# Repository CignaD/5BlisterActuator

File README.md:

# 5BlisterActuator
Example Arduino Code and Schematic for a 5 blister plunger

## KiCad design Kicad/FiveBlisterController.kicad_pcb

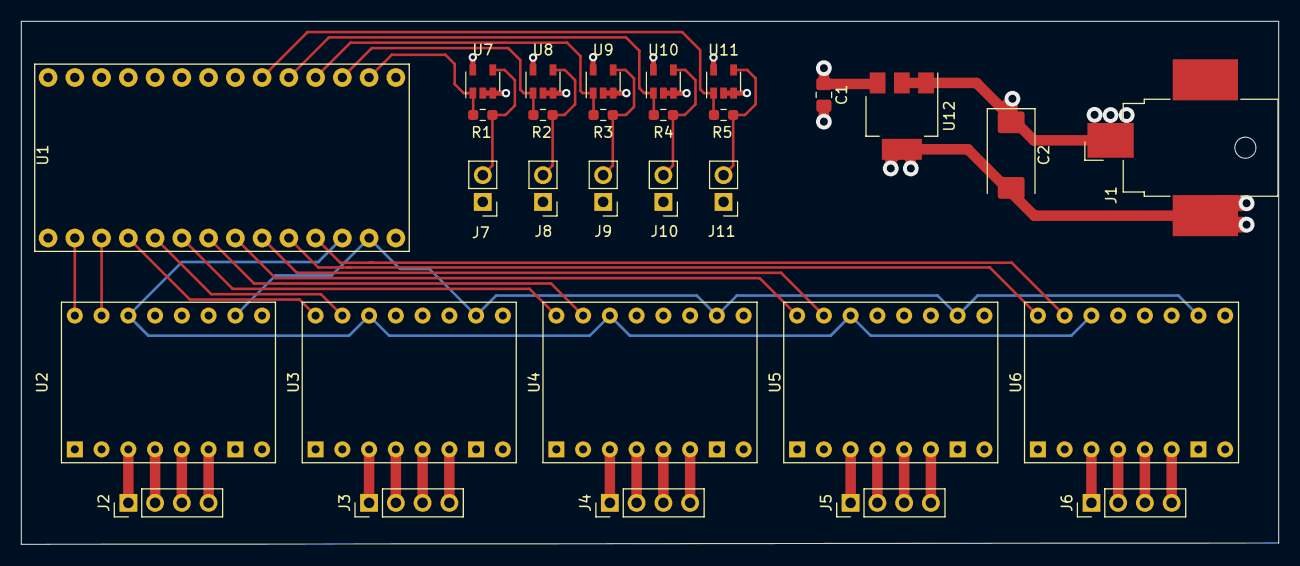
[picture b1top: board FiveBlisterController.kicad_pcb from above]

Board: 4 copper layers, 119.4 x 49.7 mm, 35 parts (0 on the bottom side), 45 nets.

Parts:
C1: 10u; C_0805_2012Metric_Pad1.18x1.45mm_HandSolder
C2: 100u; CP_EIA-7343-30_AVX-N
J1: Barrel_Jack_Switch; BarrelJack_CUI_PJ-036AH-SMT_Horizontal
J2, J3, J4, J5, J6: Conn_01x04_Male; PinHeader_1x04_P2.54mm_Vertical
J7, J8, J9, J10, J11: Conn_01x02_Male; PinHeader_1x02_P2.54mm_Vertical
R1, R2, R3, R4, R5: 2k2; R_0603_1608Metric_Pad0.98x0.95mm_HandSolder
U1: Teensy.32_simple; Teensy3.2_simple
U2, U3, U4, U5, U6: STSPIN220
U2#2, U3#2, U4#2, U5#2, U6#2: Pololu_STSPIN220; Pololu STSPIN220
U7, U8, U9, U10, U11: TLV272; SOT-23-5
U12: MC33375; SOT-223

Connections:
+3V3: C1.1, J7.1, J8.1, J9.1, J10.1, J11.1, U1.26, U2.2, U3.2, U4.2, U5.2, U6.2, U12.3
/Dir0: U1.2, U2.16
/Dir1: U1.4, U3.16
/Dir2: U1.6, U4.16
/Dir3: U1.8, U5.16
/Dir4: U1.10, U6.16
/FSR0: R1.1, U1.16, U7.1
/FSR1: R2.1, U1.17, U8.1
/FSR2: R3.1, U1.18, U9.1
/FSR3: R4.1, U1.19, U10.1
/FSR4: R5.1, U1.20, U11.1
/M1: U1.13, U2.10, U3.10, U4.10, U5.10, U6.10
/Stdby: U1.12, U2.14, U3.14, U4.14, U5.14, U6.14
/Step0: U1.3, U2.15
/Step1: U1.5, U3.15
/Step2: U1.7, U4.15
/Step3: U1.9, U5.15
/Step4: U1.11, U6.15
/Vin: C2.1, J1.1, U2.8, U3.8, U4.8, U5.8, U6.8, U7.5, U8.5, U9.5, U10.5, U11.5, U12.1, U12.2
GND: C1.2, C2.2, J1.2, U1.1, U2.1, U2.7, U2.9, U2.11, U3.1, U3.7, U3.9, U3.11, U4.1, U4.7, U4.9, U4.11, U5.1, U5.7, U5.9, U5.11, U6.1, U6.7, U6.9, U6.11, U7.2, U7.3, U8.2, U8.3, U9.2, U9.3, U10.2, U10.3, U11.2, U11.3, U12.4
unnamed: J2.1, U2.3
unnamed: J2.2, U2.4
unnamed: J2.3, U2.5
unnamed: J2.4, U2.6
unnamed: J3.1, U3.3
unnamed: J3.2, U3.4
unnamed: J3.3, U3.5
unnamed: J3.4, U3.6
unnamed: J4.1, U4.3
unnamed: J4.2, U4.4
unnamed: J4.3, U4.5
unnamed: J4.4, U4.6
unnamed: J5.1, U5.3
unnamed: J5.2, U5.4
unnamed: J5.3, U5.5
unnamed: J5.4, U5.6
unnamed: J6.1, U6.3
unnamed: J6.2, U6.4
unnamed: J6.3, U6.5
unnamed: J6.4, U6.6
unnamed: J7.2, R1.2, U7.4
unnamed: J8.2, R2.2, U8.4
unnamed: J9.2, R3.2, U9.4
unnamed: J10.2, R4.2, U10.4
unnamed: J11.2, R5.2, U11.4
